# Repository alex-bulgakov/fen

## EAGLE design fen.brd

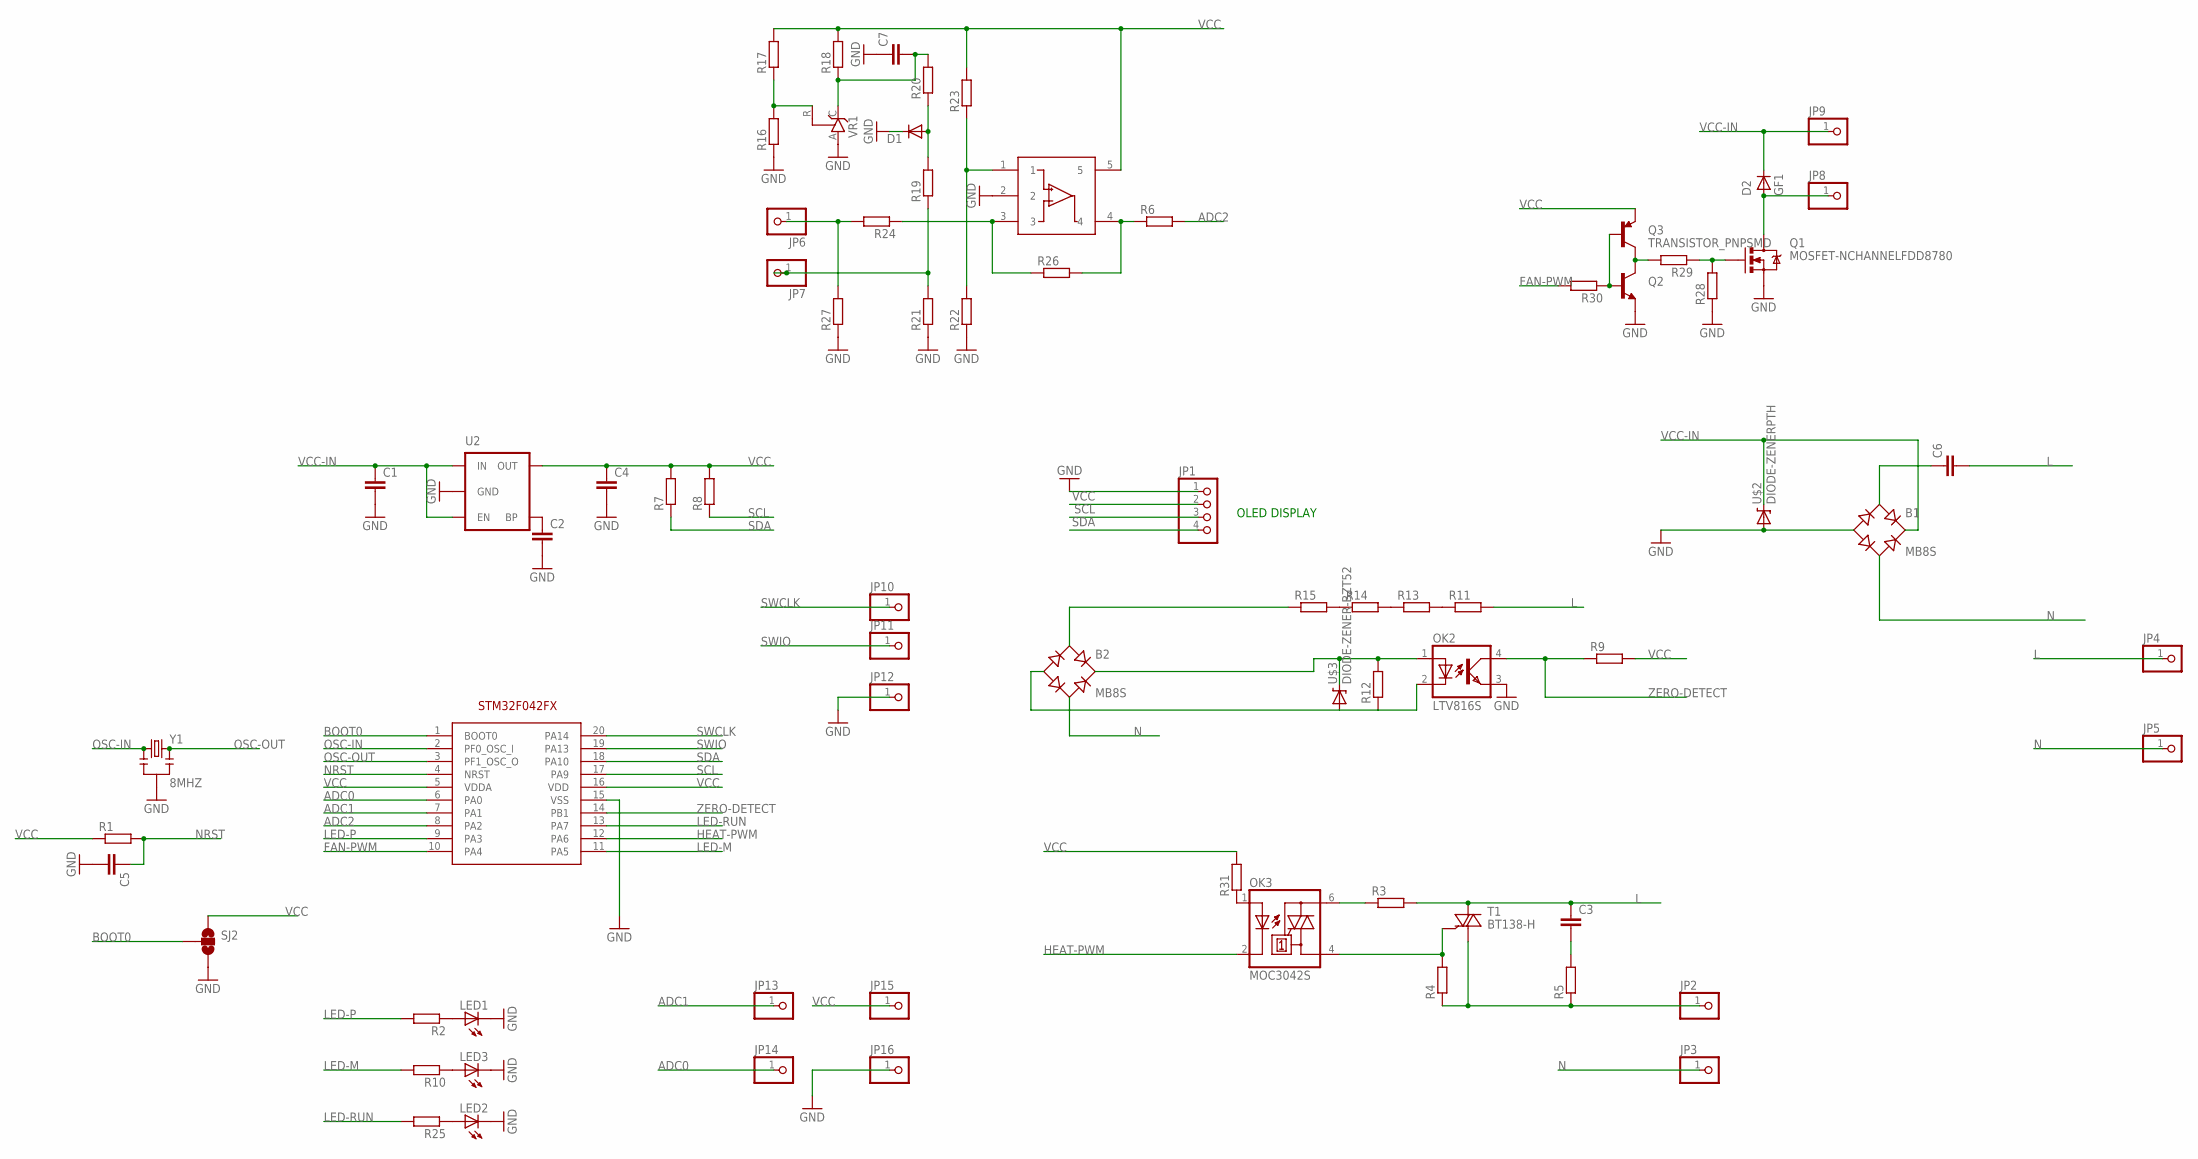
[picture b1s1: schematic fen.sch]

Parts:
B1, B2: MB8S; SOIC-4
C1, C4, C7: C-EUC0805; C0805
C2, C5: C-EUC0603; C0603
C3: C-EUC1206; C1206
C6: C-EU150-072X183; C150-072X183
D1: DIODE1N4148; DIODE-1N4148
D2: GF1; SMA-DO214AC
JP1: PINHD-1X4; 1X04
JP2, JP3, JP4, JP5, JP6, JP7, JP8, JP9, JP10, JP11, JP12, JP13, JP14, JP15, JP16: PINHD-1X1; 1X01
LED1, LED2, LED3: LED0603; LED-0603
OK2: LTV816S; SMD4
OK3: MOC3042S; DIL6-SMD
Q1: MOSFET-NCHANNELFDD8780; DPAK
Q2: TRANSISTOR_NPNSOT23; SOT23
Q3: TRANSISTOR_PNPSMD; SOT23-3
R1, R2, R6, R7, R8, R9, R10, R12, R16, R17, R18, R19, R20, R21, R22, R23, R24, R25, R26, R27, R28, R29, R30, R31: R-EU_R0603; R0603
R3, R4, R5, R11, R13, R14, R15: R-EU_R1206; R1206
SJ2: SOLDERJUMPER_2WAYS; SJ_3
T1: BT138-H; TO220BH
U1: STM32F042FX; TSSOP20
U2: MIC52053.3V; SOT23-5
U$1: LMV321M5; SOT23-5
U$2: DIODE-ZENERPTH; DIODE-ZENER
U$3: DIODE-ZENER-BZT52; SOD-323
VR1: TL431CLP; TO92-CLP
Y1: 8MHZ; RESONATOR-SMD

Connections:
ADC0: JP14.1, U1.6 (PA0)
ADC1: JP13.1, U1.7 (PA1)
ADC2: R6.2, U1.8 (PA2)
BOOT0: SJ2.2, U1.1 (BOOT0)
FAN-PWM: R30.2, U1.10 (PA4)
GND: B1.-, C1.2, C2.2, C4.2, C5.2, C7.1, D1.C, JP1.1, JP12.1, JP16.1, LED1.C, LED2.C, LED3.C, OK2.3 (EMIT), Q1.3 (S), Q2.2 (E), R16.1, R21.1, R22.1, R27.1, R28.1, SJ2.3, U1.15 (VSS), U2.2 (GND), U$1.2, U$2.P$2 (A), VR1.A, Y1.2
HEAT-PWM: OK3.2 (C), U1.12 (PA6)
L: C3.1, C6.2, JP4.1, R3.2, R11.2, T1.T2 (A2)
LED-M: R10.2, U1.11 (PA5)
LED-P: R2.2, U1.9 (PA3)
LED-RUN: R25.2, U1.13 (PA7)
N: B1.~2 (AC2), B2.~2 (AC2), JP3.1, JP5.1
unnamed: LED2.A, R25.1
unnamed: OK3.4 (A1), R4.2, T1.G
unnamed: OK3.6 (A2), R3.1
unnamed: C3.2, R5.2
unnamed: JP2.1, R4.1, R5.1, T1.T1 (A1)
unnamed: R6.1, R26.2, U$1.4
unnamed: C2.1, U2.4 (BP)
unnamed: B2.-, OK2.2 (C), R12.1, U$3.2 (A)
unnamed: B1.~1 (AC1), C6.1
unnamed: R11.1, R13.2
unnamed: R14.1, R15.2
unnamed: R13.1, R14.2
unnamed: OK3.1 (A), R31.1
unnamed: B2.+, OK2.1 (A), R12.2, U$3.1 (C)
unnamed: R16.2, R17.1, VR1.R
unnamed: D2.A, JP8.1, Q1.4 (D)
unnamed: C7.2, R18.1, R20.2, VR1.C
unnamed: R22.2, R23.1, U$1.1
unnamed: R24.1, R26.1, U$1.3
unnamed: JP6.1, R24.2, R27.2
unnamed: JP7.1, R19.1, R21.2
unnamed: D1.A, R19.2, R20.1
unnamed: Q1.1 (G), R28.2, R29.1
unnamed: Q2.3 (C), Q3.3 (C), R29.2
unnamed: Q2.1 (B), Q3.1 (B), R30.1
unnamed: B2.~1 (AC1), R15.1
unnamed: LED3.A, R10.1
unnamed: LED1.A, R2.1
NRST: C5.1, R1.2, U1.4 (NRST)
OSC-IN: U1.2 (PF0_OSC_I), Y1.1
OSC-OUT: U1.3 (PF1_OSC_O), Y1.3
SCL: JP1.3, R8.1, U1.17 (PA9)
SDA: JP1.4, R7.1, U1.18 (PA10)
SWCLK: JP10.1, U1.20 (PA14)
SWIO: JP11.1, U1.19 (PA13)
VCC: C4.1, JP1.2, JP15.1, Q3.2 (E), R1.1, R7.2, R8.2, R9.2, R17.2, R18.2, R23.2, R31.2, SJ2.1, U1.5 (VDDA), U1.16 (VDD), U2.5 (OUT), U$1.5
VCC-IN: B1.+, C1.1, D2.K (C), JP9.1, U2.1 (IN), U2.3 (EN), U$2.P$1 (C)
ZERO-DETECT: OK2.4 (COL), R9.1, U1.14 (PB1)

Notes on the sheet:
OLED DISPLAY

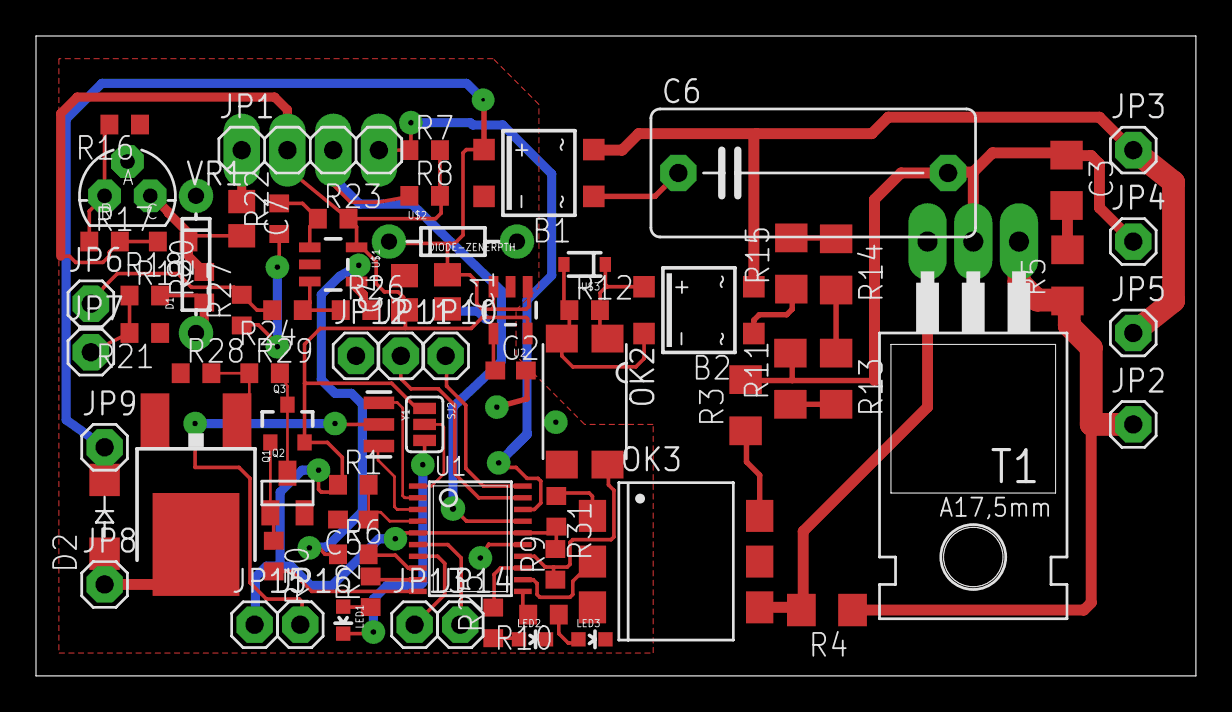
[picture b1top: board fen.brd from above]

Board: 2 copper layers, 64.4 x 35.5 mm, 75 parts (0 on the bottom side), 50 nets.

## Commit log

2017-10-06 init commit
2017-10-06 2 commit
2017-10-06 3 version
2017-10-06 add bottom img
2017-10-06 edit images
2017-10-08 change board

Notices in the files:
parts and their libraries:
SparkFun-Passives: Licensing: CC v3.0 Share-Alike You are welcome to use this library for commercial purposes.
